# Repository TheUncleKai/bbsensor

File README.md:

# bbsensor
BBQ Sensor

The 8 is a simple temperature monitor intended for BBQ/Smoker. It has 8 inlets that can be used with PTC or Pt100 probes. The BBSensor is run by a ESP8266 Microcontroller (NodeMCU Lua Lolin V3 Modul). The temperature can be delivered either via the display or network.

Front view
![Main View][view1]

Back view
![Back View][view2]

Top view
![Top View][view3]

[view1]: prj/BBSensor_01.png
[view2]: prj/BBSensor_02.png
[view3]: prj/BBSensor_03.png

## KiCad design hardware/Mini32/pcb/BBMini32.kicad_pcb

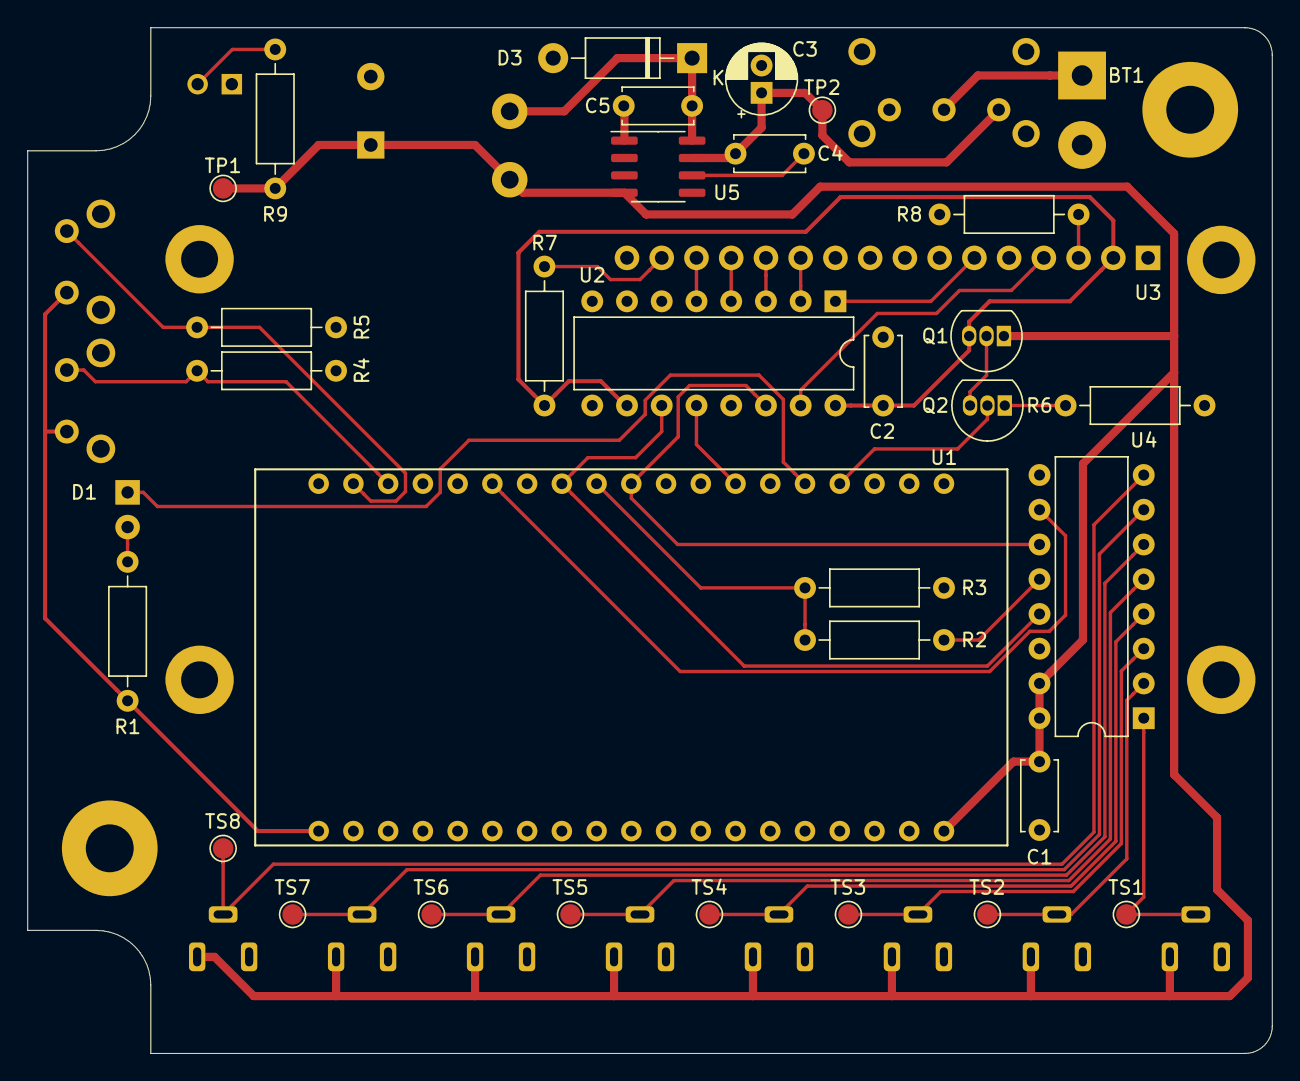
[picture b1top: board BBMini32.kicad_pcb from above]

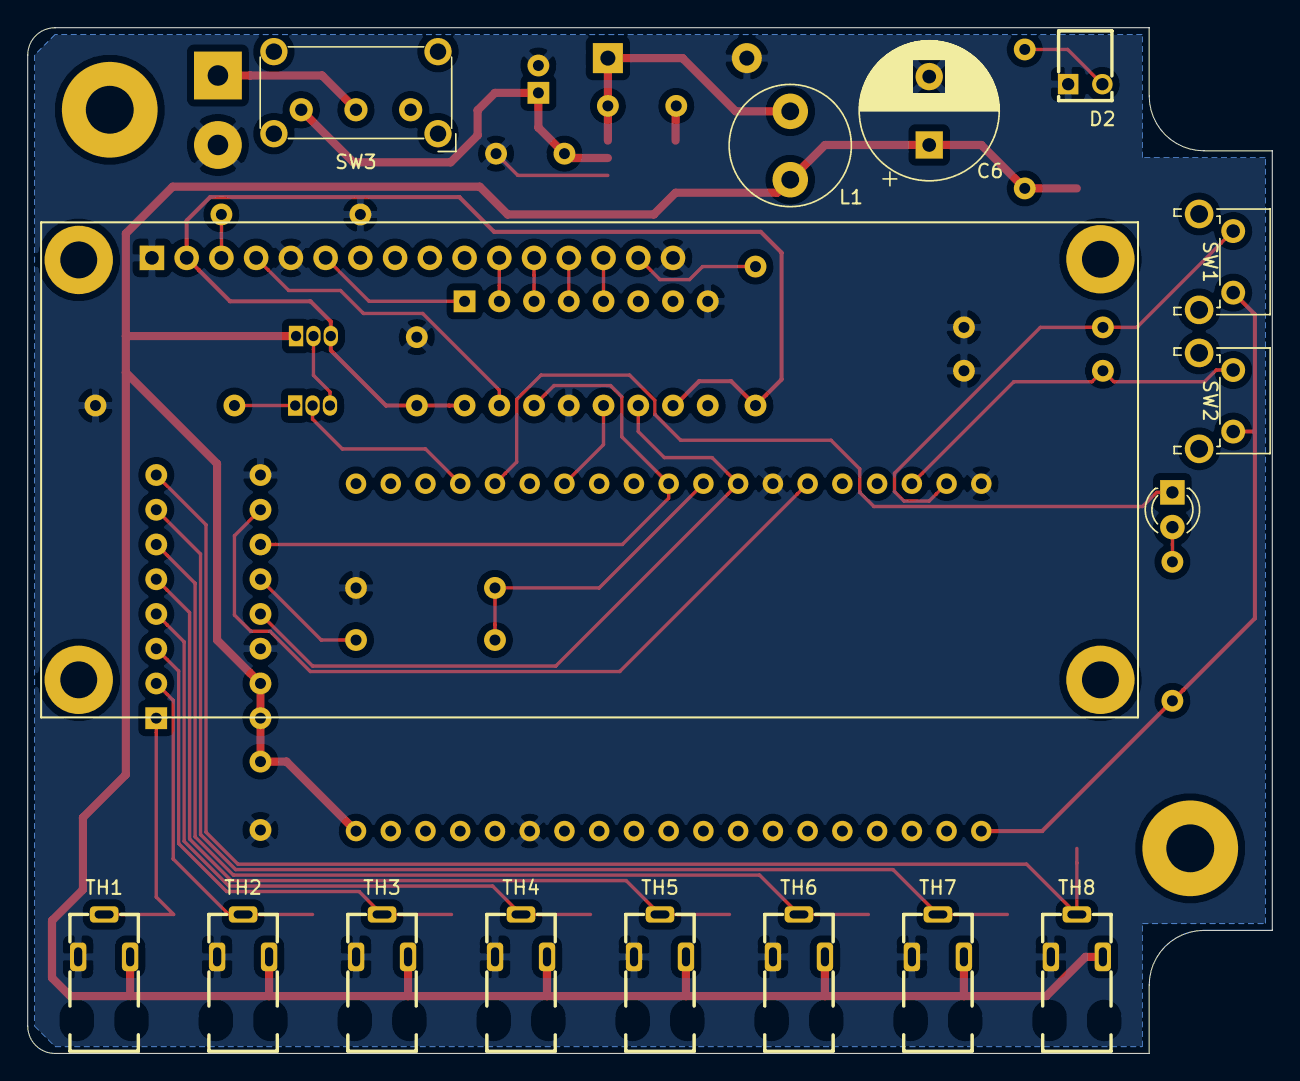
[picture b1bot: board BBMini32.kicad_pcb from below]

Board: 2 copper layers, 91.0 x 75.0 mm, 48 parts (16 on the bottom side), 38 nets.

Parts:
BT1: Battery_Cell; SolderWirePad_1x02_P5.08mm_Drill1.5mm
C1, C2, C4: 100n; C_Disc_D5.0mm_W2.5mm_P5.00mm
C3: 100u; CP_Radial_D5.0mm_P2.00mm
C5: 10n; C_Disc_D5.0mm_W2.5mm_P5.00mm
C6: 68u; CP_Radial_D10.0mm_P5.00mm
D1: GREEN; LED_D3.0mm
D2: POWER; 5600F
D3: 1N5819; D_DO-41_SOD81_P10.16mm_Horizontal
L1: 47u; L_Radial_D8.7mm_P5.00mm_Fastron_07HCP
Q1: S8550; TO-92_Inline
Q2: S8050; TO-92_Inline
R1: 140; R_Axial_DIN0207_L6.3mm_D2.5mm_P10.16mm_Horizontal
R2: 1k; R_Axial_DIN0207_L6.3mm_D2.5mm_P10.16mm_Horizontal
R3, R4, R5: 2k2; R_Axial_DIN0207_L6.3mm_D2.5mm_P10.16mm_Horizontal
R6: 270; R_Axial_DIN0207_L6.3mm_D2.5mm_P10.16mm_Horizontal
R7, R9: 220; R_Axial_DIN0207_L6.3mm_D2.5mm_P10.16mm_Horizontal
R8: 2k; R_Axial_DIN0207_L6.3mm_D2.5mm_P10.16mm_Horizontal
SW1, SW2: SW_Push; SW_Tactile_SPST_Angled_PTS645Vx83-2LFS
SW3: SW_SPDT; SW_E-Switch_EG1224_SPDT_Angled
TH1, TH2, TH3, TH4, TH5, TH6, TH7, TH8: AudioJack3; LUMBERG_1501_05
TP1, TP2: TestPoint; TestPoint_Pad_D1.5mm
TS1, TS2, TS3, TS4, TS5, TS6, TS7, TS8: TestPoint; TestPoint_Pad_D1.5mm
U1: ESP-32_NodeMCU
U2: 74HC595; DIP-16_W7.62mm
U3: HD44780; HD44780_LCD_2x16
U4: MCP3208; DIP-16_W7.62mm
U5: LM2672M-5.0; SOIC-8_3.9x4.9mm_P1.27mm

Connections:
+3V3: R1.1, SW1.2, SW2.2, U1.1
+5V: C1.1, C6.1, L1.2, Q1.1, R9.1, TH1.R, TH2.R, TH3.R, TH4.R, TH5.R, TH6.R, TH7.R, TH8.R, TP1.1, U1.19, U4.15, U4.16, U5.4
/CS1: U1.25, U4.10
/CS2: U1.32, U2.12
/DB4: U2.2, U3.11
/DB5: U2.3, U3.12
/DB6: U2.4, U3.13
/DB7: U2.5, U3.14
/ENABLE: U2.1, U3.6
/MISO: R2.1, U4.12
/MISO_5V: R2.2, R3.1, U1.28
/MOSI: U1.29, U2.14, U4.11
/RS: U2.15, U3.4
/SCLK: U1.27, U2.11, U4.13
/SIGNAL1: TH1.T, TS1.1, U4.1
/SIGNAL2: TH2.T, TS2.1, U4.2
/SIGNAL3: TH3.T, TS3.1, U4.3
/SIGNAL4: TH4.T, TS4.1, U4.4
/SIGNAL5: TH5.T, TS5.1, U4.5
/SIGNAL6: TH6.T, TS6.1, U4.6
/SIGNAL7: TH7.T, TS7.1, U4.7
/SIGNAL8: TH8.T, TS8.1, U4.8
/VDISP: C2.1, Q1.3, R7.1, U2.10, U2.16, U3.2
/VIN: C3.1, C4.1, SW3.3, TP2.1, U5.7
/VPOWER: BT1.1, SW3.2
GND: BT1.2, C1.2, C2.2, C3.2, C4.2, C6.2, D2.1, D3.2, R3.2, R4.2, R5.2, R6.2, R8.2, TH1.S, TH2.S, TH3.S, TH4.S, TH5.S, TH6.S, TH7.S, TH8.S, U1.14, U1.20, U1.26, U2.8, U2.13, U3.1, U3.5, U3.16, U4.9, U4.14, U5.6
unnamed: C5.1, D3.1, L1.1, U5.8
unnamed: C5.2, U5.1
unnamed: D1.1, U1.34
unnamed: D1.2, R1.2
unnamed: D2.2, R9.2
unnamed: Q1.2, Q2.3
unnamed: Q2.1, R6.1
unnamed: Q2.2, U1.35
unnamed: R4.1, SW2.1, U1.22
unnamed: R5.1, SW1.1, U1.21
unnamed: R7.2, U3.15
unnamed: R8.1, U3.3

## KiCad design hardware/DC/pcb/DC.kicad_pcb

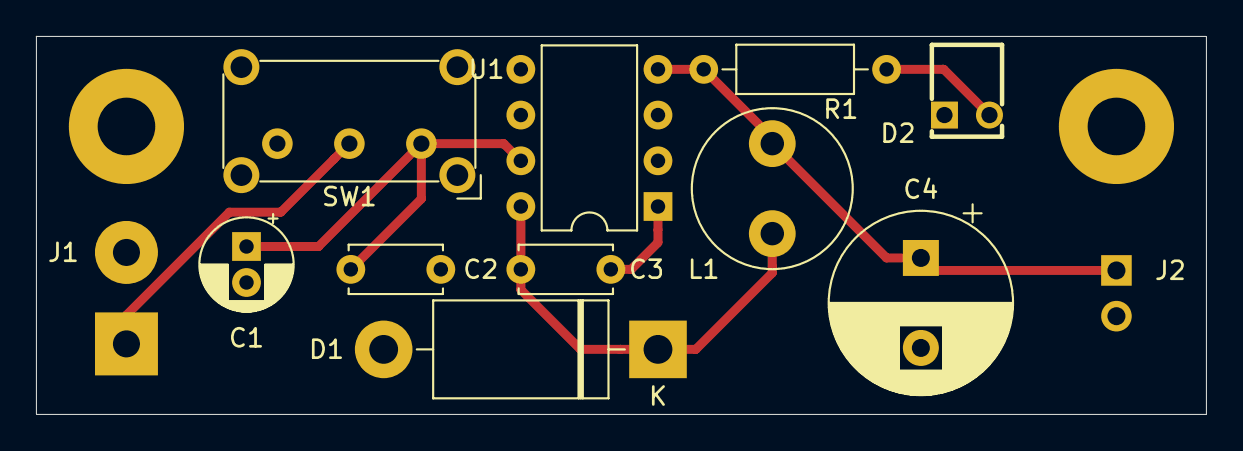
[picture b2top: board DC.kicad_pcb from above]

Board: 2 copper layers, 65.0 x 21.0 mm, 12 parts (1 on the bottom side), 7 nets.

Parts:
C1: 100u; CP_Radial_D5.0mm_P2.00mm
C2: 100n; C_Disc_D5.0mm_W2.5mm_P5.00mm
C3: 10n; C_Disc_D5.0mm_W2.5mm_P5.00mm
C4: 68u; CP_Radial_D10.0mm_P5.00mm
D1: 1N5822; D_DO-201AD_P15.24mm_Horizontal
D2: POWER; 5600F
J1: POWER; SolderWirePad_1x02_P5.08mm_Drill1.5mm
J2: OUTPUT; PinSocket_1x02_P2.54mm_Vertical
L1: 47u; L_Radial_D8.7mm_P5.00mm_Fastron_07HCP
R1: 220; R_Axial_DIN0207_L6.3mm_D2.5mm_P10.16mm_Horizontal
SW1: SW_SPDT; SW_E-Switch_EG1224_SPDT_Angled
U1: LM2672M-5.0; DIP-8_W7.62mm

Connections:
+5V: C4.1, J2.1, L1.2, R1.1, U1.4
/VIN: C1.1, C2.1, SW1.1, U1.7
/VPOWER: J1.1, SW1.2
GND: C1.2, C2.2, C4.2, D1.2, D2.1, J1.2, J2.2, U1.6
unnamed: C3.1, D1.1, L1.1, U1.8
unnamed: C3.2, U1.1
unnamed: D2.2, R1.2

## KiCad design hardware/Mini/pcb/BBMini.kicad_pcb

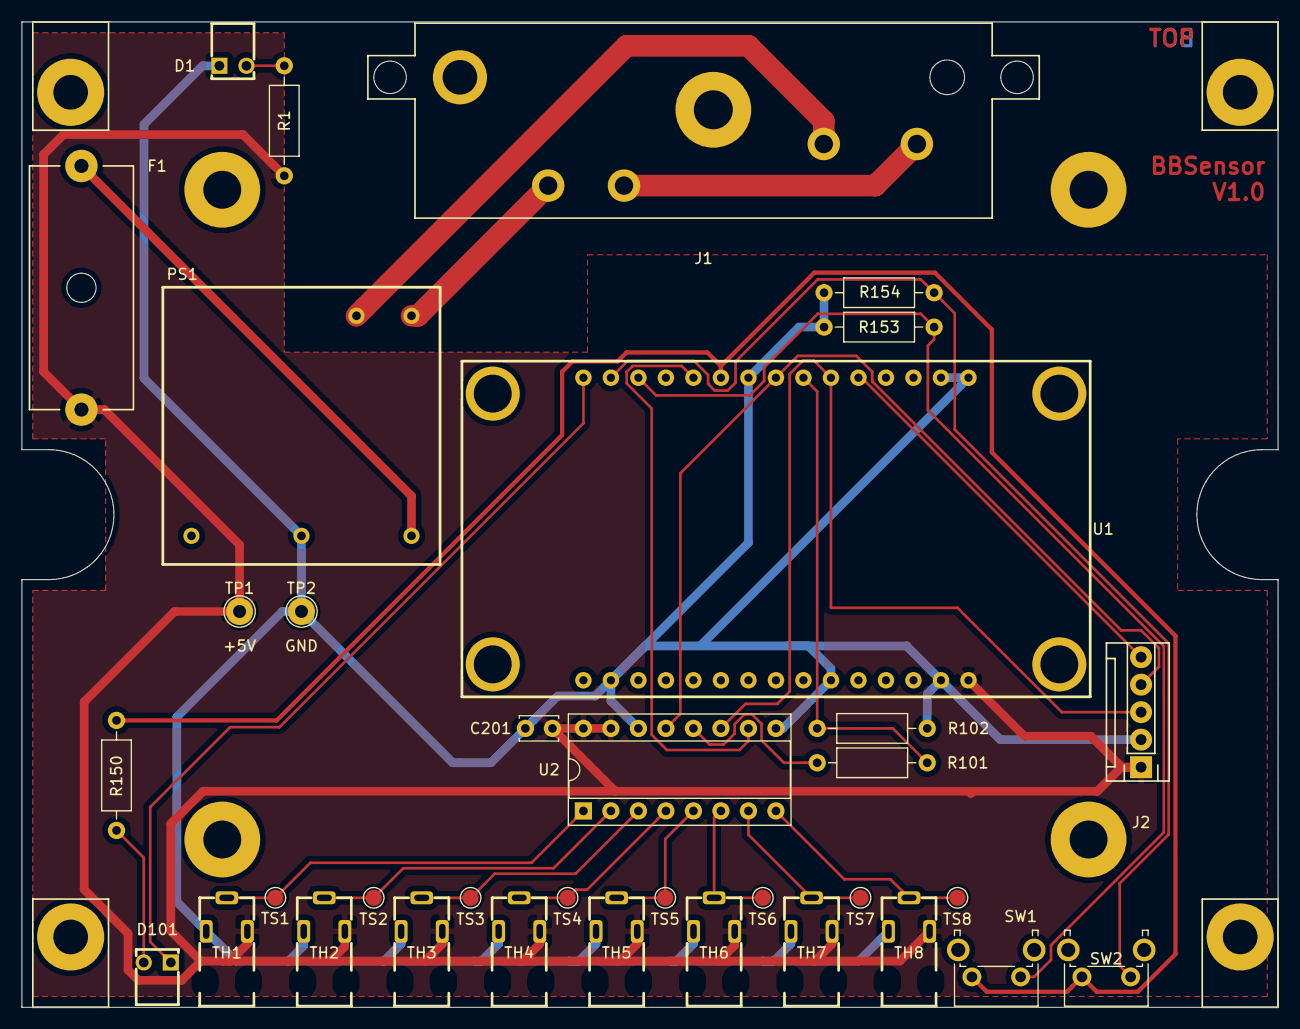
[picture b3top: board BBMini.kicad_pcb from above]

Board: 2 copper layers, 116.0 x 91.0 mm, 35 parts (0 on the bottom side), 26 nets.

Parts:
C201: 100n; C_Disc_D3.4mm_W2.1mm_P2.50mm
D1: POWER; 5600F
D101: GREEN; 5600F
F1: Fuse; Fuse_holder_20x5_22.5
J1: Schurter_CMF1; CMF1_Offset
J2: Display; Molex_KK256_Pin_Header_Straight_1x05
PS1: TMPS_05; Traco_TMPS_05
R1: 220; R_Axial_DIN0207_L6.3mm_D2.5mm_P10.16mm_Horizontal
R101: 1k; R_Axial_DIN0207_L6.3mm_D2.5mm_P10.16mm_Horizontal
R102, R153, R154: 2k2; R_Axial_DIN0207_L6.3mm_D2.5mm_P10.16mm_Horizontal
R150: 140; R_Axial_DIN0207_L6.3mm_D2.5mm_P10.16mm_Horizontal
SW1, SW2: SW_Push; SW_Tactile_SPST_Angled_PTS645Vx83-2LFS
TH1, TH2, TH3, TH4, TH5, TH6, TH7, TH8: AudioJack3; LUMBERG_1501_05
TP1, TP2: TestPoint; TestPoint_THTPad_D2.5mm_Drill1.2mm
TS1, TS2, TS3, TS4, TS5, TS6, TS7, TS8: TestPoint; TestPoint_Pad_D1.5mm
U1: ESP8266-12E_NodeMCU_Lolin
U2: MCP3208; DIP-16_W7.62mm_Socket

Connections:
+3V3: R150.1, SW1.2, SW2.2, U1.21
+5V: C201.1, F1.1, J2.1, R1.2, TH1.R, TH2.R, TH3.R, TH4.R, TH5.R, TH6.R, TH7.R, TH8.R, TP1.1, U1.15, U2.15, U2.16
/Analog/Digital/SIGNAL1: TH1.T, TS1.1, U2.1
/Analog/Digital/SIGNAL2: TH2.T, TS2.1, U2.2
/Analog/Digital/SIGNAL3: TH3.T, TS3.1, U2.3
/Analog/Digital/SIGNAL4: TH4.T, TS4.1, U2.4
/Analog/Digital/SIGNAL5: TH5.T, TS5.1, U2.5
/Analog/Digital/SIGNAL6: TH6.T, TS6.1, U2.6
/Analog/Digital/SIGNAL7: TH7.T, TS7.1, U2.7
/Analog/Digital/SIGNAL8: TH8.T, TS8.1, U2.8
/Analog/Digital/SPI1: J2.3, U1.25, U2.11
/Analog/Digital/SPI2: R101.1, U2.12
/Analog/Digital/SPI3: J2.4, U1.23, U2.13
/Analog/Digital/SPI4: U1.20, U2.10
/Display/SPI5: J2.5, U1.26
/ESP8266/BUTTON1: R153.1, SW1.1, U1.18
/ESP8266/BUTTON2: R154.1, SW2.1, U1.17
/ESP8266/LED: D101.1, U1.16
/ESP8266/MISO: R101.2, R102.1, U1.24
GND: C201.2, D1.1, J2.2, PS1.4, R102.2, R153.2, R154.2, TH1.S, TH2.S, TH3.S, TH4.S, TH5.S, TH6.S, TH7.S, TH8.S, TP2.1, U1.2, U1.10, U1.14, U1.22, U1.29, U1.30, U2.9, U2.14
unnamed: D1.2, R1.1
unnamed: D101.2, R150.2
unnamed: F1.2, PS1.5
unnamed: J1.1, PS1.2
unnamed: J1.2, J1.4
unnamed: J1.3, PS1.1

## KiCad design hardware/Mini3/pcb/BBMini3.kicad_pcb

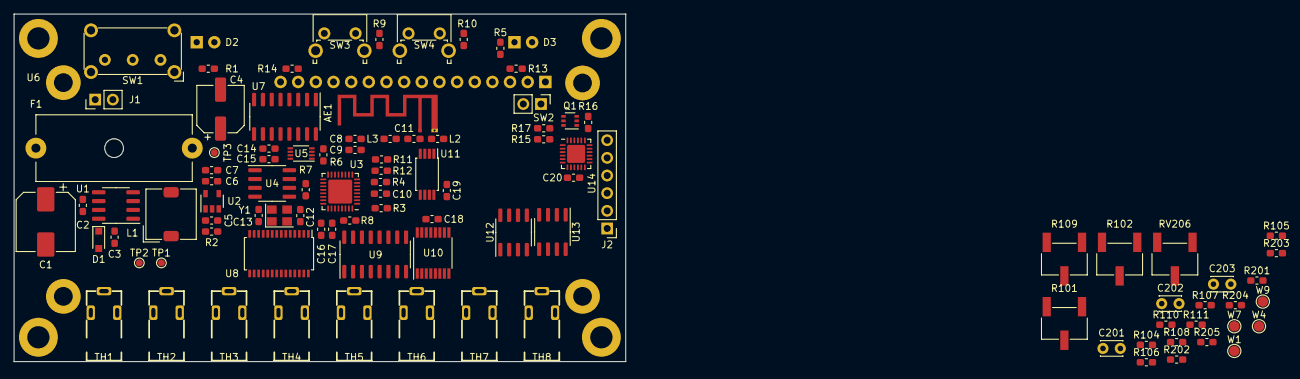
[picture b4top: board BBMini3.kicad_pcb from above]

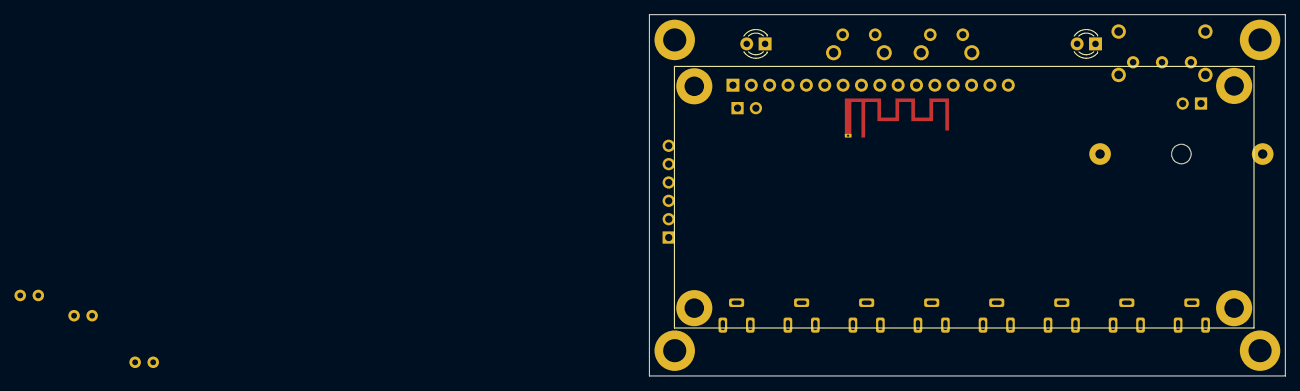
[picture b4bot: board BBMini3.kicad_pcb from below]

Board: 4 copper layers, 88.0 x 50.0 mm, 101 parts (3 on the bottom side), 94 nets, no tracks yet.

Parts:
AE1: Antenna_Shield; Texas_SWRA117D_2.4GHz_Left
C1: 100u; CP_Elec_8x10
C2, C8, C9, C10, C14, C15, C16, C17, C18, C19, C20: 100n; C_0603_1608Metric_Pad1.05x0.95mm_HandSolder
C3: 10n; C_0603_1608Metric_Pad1.05x0.95mm_HandSolder
C4: 68u; CP_Elec_6.3x5.9
C5, C6: 10u; C_0603_1608Metric_Pad1.05x0.95mm_HandSolder
C7: 1u; C_0603_1608Metric_Pad1.05x0.95mm_HandSolder
C11: 5p6; C_0603_1608Metric_Pad1.05x0.95mm_HandSolder
C12, C13: 10p; C_0603_1608Metric_Pad1.05x0.95mm_HandSolder
C201, C202, C203: 100n; C_Disc_D3.0mm_W2.0mm_P2.50mm
D1: 1N5822; D_SOD-323_HandSoldering
D2: POWER; LED_D3.0mm
D3: LED; LED_D3.0mm
F1: Fuse; Fuse_holder_20x5_22.5
J1: Conn_01x02; PinHeader_1x02_P2.54mm_Vertical
J2: USB_B_Mini; PinHeader_1x06_P2.54mm_Vertical
L1: 47u; L_TDK_SLF7032
L2, L3: L; L_0603_1608Metric_Pad1.05x0.95mm_HandSolder
Q1: MBT2222ADW1T1; SOT-363_SC-70-6
R1, R14: 220; R_0603_1608Metric_Pad1.05x0.95mm_HandSolder
R2, R3, R4, R6, R15, R16, R17, R105, R106, R201, R202, R203, R205: 10k; R_0603_1608Metric_Pad1.05x0.95mm_HandSolder
R5: 140; R_0603_1608Metric_Pad1.05x0.95mm_HandSolder
R7, R108, R110: 200; R_0603_1608Metric_Pad1.05x0.95mm_HandSolder
R8: 12k; R_0603_1608Metric_Pad1.05x0.95mm_HandSolder
R9, R10, R12, R104: 2k2; R_0603_1608Metric_Pad1.05x0.95mm_HandSolder
R11: 1k; R_0603_1608Metric_Pad1.05x0.95mm_HandSolder
R13, R111: 2k; R_0603_1608Metric_Pad1.05x0.95mm_HandSolder
R101: 405; Potentiometer_Bourns_3269W_Vertical
R102: 300; Potentiometer_Bourns_3269W_Vertical
R107: 4k7; R_0603_1608Metric_Pad1.05x0.95mm_HandSolder
R109: 470; Potentiometer_Bourns_3269W_Vertical
R204: 100k; R_0603_1608Metric_Pad1.05x0.95mm_HandSolder
RV206: 10k; Potentiometer_Bourns_3269W_Vertical
SW1: SW_SPDT; SW_E-Switch_EG1224_SPDT_Angled
SW2: SW_Push; PinHeader_1x02_P2.54mm_Vertical
SW3, SW4: SW_Push; SW_Tactile_SPST_Angled_PTS645Vx83-2LFS
TH1, TH2, TH3, TH4, TH5, TH6, TH7, TH8: AudioJack3; LUMBERG_1501_05
TP1, TP2, TP3: TestPoint; TestPoint_Pad_D1.0mm
U1: LM2672M-5.0; SOIC-8_3.9x4.9mm_P1.27mm
U2: AP2112K-3.3; SOT-23-5
U3: ESP8266EX; QFN-32-1EP_5x5mm_P0.5mm_EP3.45x3.45mm
U4: AT25SF081-SSHF-X; SOIC-8_3.9x4.9mm_P1.27mm
U5: SN74LVC1G139; VSSOP-8_2.3x2mm_P0.5mm
U6: HD44780; HD44780_LCD_2x16
U7, U9: 74HC595; SOIC-16_3.9x9.9mm_P1.27mm
U8: ADG707; TSSOP-28_4.4x9.7mm_P0.65mm
U10: ADG709; TSSOP-16_4.4x5mm_P0.65mm
U11: MCP3202; TSSOP-8_4.4x3mm_P0.65mm
U12, U13: OPA2340; SOIC-8_3.9x4.9mm_P1.27mm
U14: CP2104; QFN-24-1EP_4x4mm_P0.5mm_EP2.6x2.6mm
W1, W4, W7, W9: TestPoint_Pad_D1.5mm
Y1: ABM8-26.000MHZ-10-1-U-T; Crystal_SMD_Abracon_ABM8G-4Pin_3.2x2.5mm

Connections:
+3V3: C6.2, C7.2, C8.1, C9.2, C10.2, C15.2, C20.1, R3.2, R4.2, R5.2, R6.2, SW3.1, SW4.1, TP3.1, U2.5, U3.1, U3.3, U3.4, U3.11, U3.17, U3.29, U3.30, U4.8, U5.8, U14.5, U14.6, U14.7
+5V: C4.1, C5.2, C14.1, C16.1, C17.1, C18.2, C19.2, L1.2, R1.2, R2.2, R14.1, R102.2, R102.3, R105.1, TH1.S, TH2.S, TH3.S, TH4.S, TH5.S, TH6.S, TH7.S, TH8.S, TP2.1, U1.4, U2.1, U6.2, U7.10, U7.16, U8.1, U9.10, U9.16, U10.14, U11.8, U12.8, U13.8
/ESP8266EX/CS1: U5.6, U11.1
/ESP8266EX/CS2: U5.5, U9.12
/ESP8266EX/DB4: U6.11, U7.2
/ESP8266EX/DB5: U6.12, U7.3
/ESP8266EX/DB6: U6.13, U7.4
/ESP8266EX/DB7: U6.14, U7.5
/ESP8266EX/EN: R4.1, U3.7
/ESP8266EX/ENABLE: U6.6, U7.1
/ESP8266EX/GPIO0: Q1.6, U3.15
/ESP8266EX/GPIO1_TXD: U3.25, U14.20
/ESP8266EX/GPIO2: R6.1, U3.14, U5.1
/ESP8266EX/GPIO3_RXD: R15.2, U3.26
/ESP8266EX/GPIO4: R9.1, SW3.2, U3.16
/ESP8266EX/GPIO5: R10.1, SW4.2, U3.24
/ESP8266EX/GPIO12: R11.2, U3.10
/ESP8266EX/GPIO15: U3.13, U5.2
/ESP8266EX/GPIO16: D3.2, U3.8
/ESP8266EX/LNA: C11.2, L3.1, U3.2
/ESP8266EX/MISO: R11.1, R12.2, U11.6
/ESP8266EX/MOSI: U3.12, U7.14, U9.14, U11.5
/ESP8266EX/RS: U6.4, U7.15
/ESP8266EX/SCLK: U3.9, U7.11, U9.11, U11.7
/ESP8266EX/SDIO_CLK: R7.2, U3.21
/ESP8266EX/SDIO_CMD: U3.20, U4.1
/ESP8266EX/SDIO_DATA_0: U3.22, U4.2
/ESP8266EX/SDIO_DATA_1: U3.23, U4.5
/ESP8266EX/SDIO_DATA_2: U3.18, U4.7
/ESP8266EX/SDIO_DATA_3: U3.19, U4.3
/ESP8266EX/XTAL_IN: C13.2, U3.28, Y1.1
/ESP8266EX/XTAL_OUT: C12.2, U3.27, Y1.3
/ESP8266EX/~RST: Q1.4, R3.1, SW2.1, U3.32
/Processing/PTC1: R201.1, R202.1, U10.5
/Processing/PTC2: R203.1, R204.1, U10.6
/Processing/PTC3: R205.1, RV206.1, RV206.2, U10.7
/Processing/RTD1: R104.2, U10.4, U12.2, U13.3, W4.1
/Processing/RTD2: U10.10, U12.1, U12.5
/Processing/SIGNAL: C201.1, C202.1, C203.1, R101.2, R101.3, R201.2, R203.2, R205.2, U11.2, U13.1, W1.1
/Serial/DTR: Q1.1, R17.1, U14.23
/Serial/RTS: Q1.3, R16.1, U14.19
/Serial/USB_RX: R15.1, U14.21
/Temperature/DA: U8.28, U10.8
/Temperature/DB: U8.2, U10.9
/Temperature/S1A: TH1.R, U8.19
/Temperature/S1B: TH1.T, U8.11
/Temperature/S2A: TH2.R, U8.20
/Temperature/S2B: TH2.T, U8.10
/Temperature/S3A: TH3.R, U8.21
/Temperature/S3B: TH3.T, U8.9
/Temperature/S4A: TH4.R, U8.22
/Temperature/S4B: TH4.T, U8.8
/Temperature/S5A: TH5.R, U8.23
/Temperature/S5B: TH5.T, U8.7
/Temperature/S6A: TH6.R, U8.24
/Temperature/S6B: TH6.T, U8.6
/Temperature/S7A: TH7.R, U8.25
/Temperature/S7B: TH7.T, U8.5
/Temperature/S8A: TH8.R, U8.26
/Temperature/S8B: TH8.T, U8.4
CS0: U5.7, U7.12
GND: AE1.2, C1.2, C2.2, C4.2, C5.1, C6.1, C7.1, C8.2, C9.1, C10.1, C12.1, C13.1, C14.2, C15.1, C16.2, C17.2, C18.1, C19.1, C20.2, C201.2, C202.2, C203.2, D1.2, D2.1, J1.2, J2.5, J2.6, L2.2, L3.2, R8.2, R9.2, R10.2, R12.1, R13.2, R106.1, R111.2, R202.2, R204.2, RV206.3, SW2.2, TP1.1, U1.6, U2.2, U3.33, U4.4, U5.4, U6.1, U6.5, U6.16, U7.8, U7.13, U8.12, U8.27, U9.8, U9.13, U10.3, U10.15, U11.4, U12.4, U13.4, U14.2, U14.25, Y1.2, Y1.4
unnamed: AE1.1, C11.1, L2.1
unnamed: C1.1, C2.1, F1.1, U1.7
unnamed: C3.1, D1.1, L1.1, U1.8
unnamed: C3.2, U1.1
unnamed: D2.2, R1.1
unnamed: D3.1, R5.1
unnamed: F1.2, SW1.1
unnamed: J1.1, SW1.2
unnamed: J2.1, U14.8
unnamed: J2.2, U14.4
unnamed: J2.3, U14.3
unnamed: Q1.2, R16.2
unnamed: Q1.5, R17.2
unnamed: R2.1, U2.3
unnamed: R7.1, U4.6
unnamed: R8.1, U3.31
unnamed: R13.1, U6.3
unnamed: R14.2, U6.15
unnamed: R101.1, R107.2
unnamed: R102.1, R104.1
unnamed: R105.2, R106.2, U12.3
unnamed: R107.1, R108.2, U13.2, W7.1
unnamed: R108.1, R110.2, U12.7
unnamed: R109.1, R111.1
unnamed: R109.2, R109.3, R110.1, U12.6, W9.1
unnamed: U8.15, U9.2
unnamed: U8.16, U9.1
unnamed: U8.17, U9.15
unnamed: U8.18, U9.3
unnamed: U9.4, U10.1
unnamed: U9.6, U10.2
unnamed: U9.5, U10.16

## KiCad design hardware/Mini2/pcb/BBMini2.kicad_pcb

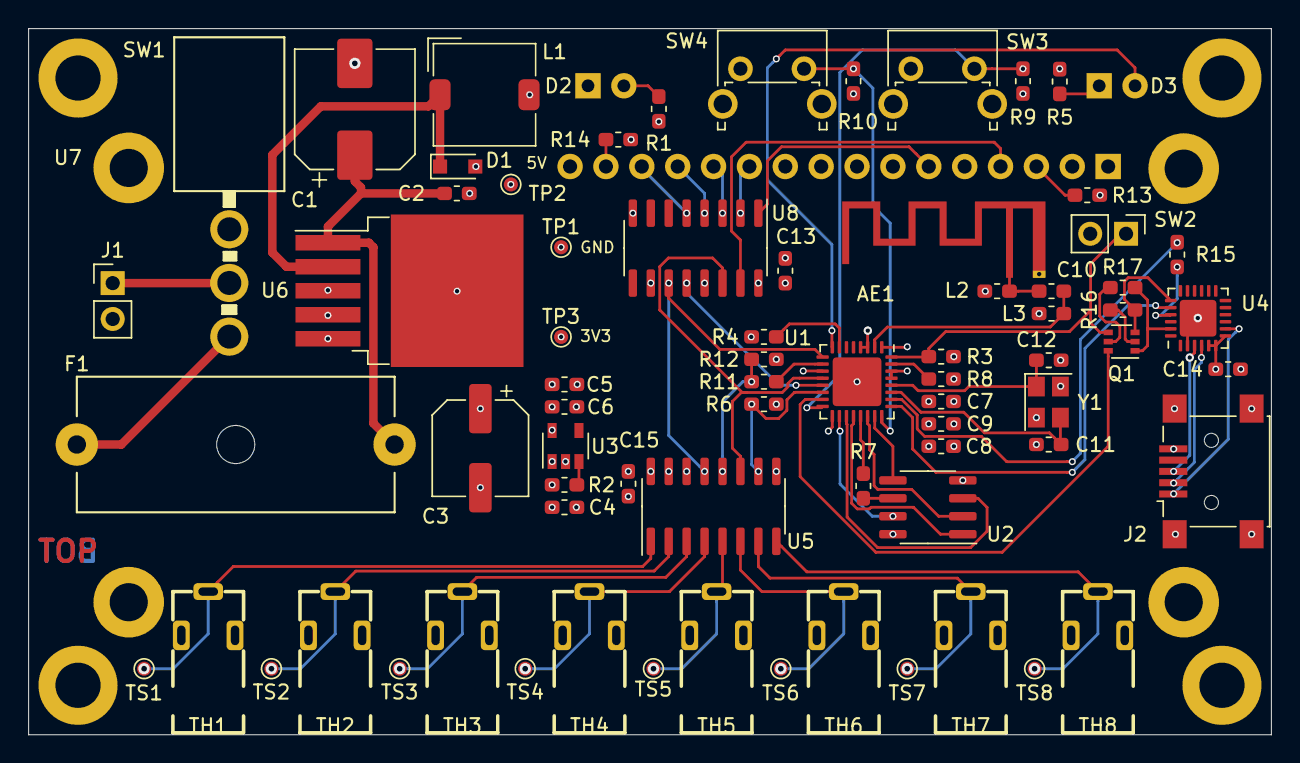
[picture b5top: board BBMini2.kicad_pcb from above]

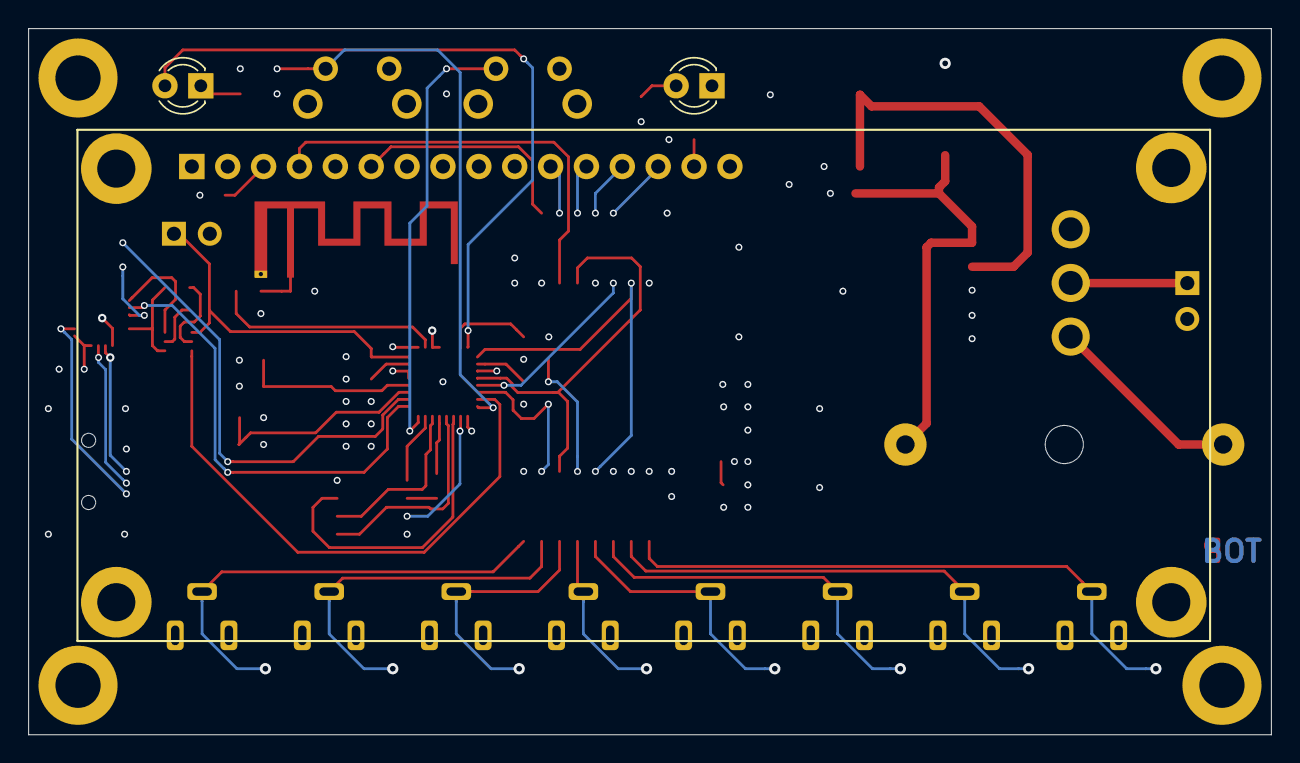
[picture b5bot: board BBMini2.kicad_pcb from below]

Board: 4 copper layers, 88.0 x 50.0 mm, 75 parts (3 on the bottom side), 60 nets.

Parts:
AE1: Antenna_Shield; Texas_SWRA117D_2.4GHz_Left
C1: 100u; CP_Elec_8x10
C2, C7, C8, C9, C13, C14, C15: 100n; C_0603_1608Metric_Pad1.05x0.95mm_HandSolder
C3: 100u; CP_Elec_6.3x5.9
C4, C5: 10u; C_0603_1608Metric_Pad1.05x0.95mm_HandSolder
C6: 1u; C_0603_1608Metric_Pad1.05x0.95mm_HandSolder
C10: 5p6; C_0603_1608Metric_Pad1.05x0.95mm_HandSolder
C11, C12: 10p; C_0603_1608Metric_Pad1.05x0.95mm_HandSolder
D1: 1N5822; D_SOD-323_HandSoldering
D2: POWER; LED_D3.0mm
D3: LED; LED_D3.0mm
F1: Fuse; Fuse_holder_20x5_22.5
J1: Conn_01x02; PinHeader_1x02_P2.54mm_Vertical
J2: USB_B_Mini; USB_Mini-B_Lumberg_2486_01_Horizontal
L1: 100u; L_TDK_SLF7032
L2, L3: L; L_0603_1608Metric_Pad1.05x0.95mm_HandSolder
Q1: MBT2222ADW1T1; SOT-363_SC-70-6
R1, R14: 220; R_0603_1608Metric_Pad1.05x0.95mm_HandSolder
R2, R3, R4, R6, R15, R16, R17: 10k; R_0603_1608Metric_Pad1.05x0.95mm_HandSolder
R5: 140; R_0603_1608Metric_Pad1.05x0.95mm_HandSolder
R7: 200; R_0603_1608Metric_Pad1.05x0.95mm_HandSolder
R8: 12k; R_0603_1608Metric_Pad1.05x0.95mm_HandSolder
R9, R10, R12: 2k2; R_0603_1608Metric_Pad1.05x0.95mm_HandSolder
R11: 1k; R_0603_1608Metric_Pad1.05x0.95mm_HandSolder
R13: 2k; R_0603_1608Metric_Pad1.05x0.95mm_HandSolder
SW1: SW_SPDT; MIYAMA_MS-500-B-VT
SW2: SW_Push; PinHeader_1x02_P2.54mm_Vertical
SW3, SW4: SW_Push; SW_Tactile_SPST_Angled_PTS645Vx83-2LFS
TH1, TH2, TH3, TH4, TH5, TH6, TH7, TH8: AudioJack3; LUMBERG_1501_05
TP1, TP2, TP3: TestPoint; TestPoint_Pad_D1.0mm
TS1, TS2, TS3, TS4, TS5, TS6, TS7, TS8: TestPoint; TestPoint_Pad_D1.0mm
U1: ESP8266EX; QFN-32-1EP_5x5mm_P0.5mm_EP3.45x3.45mm
U2: AT25SF081-SSHF-X; SOIC-8_3.9x4.9mm_P1.27mm
U3: AP2112K-3.3; SOT-23-5
U4: CP2104; QFN-24-1EP_4x4mm_P0.5mm_EP2.6x2.6mm
U5: MCP3208; SOIC-16_3.9x9.9mm_P1.27mm
U6: LM2576S-5; TO-263-5_TabPin3
U7: HD44780; HD44780_LCD_2x16
U8: 74HC595; SOIC-16_3.9x9.9mm_P1.27mm
Y1: ABM8-26.000MHZ-10-1-U-T; Crystal_SMD_Abracon_ABM8G-4Pin_3.2x2.5mm

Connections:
+3V3: C5.2, C6.2, C7.1, C8.2, C9.2, C14.1, R3.2, R4.2, R5.2, R6.2, SW3.1, SW4.1, TP3.1, U1.1, U1.3, U1.4, U1.11, U1.17, U1.29, U1.30, U2.8, U3.5, U4.5, U4.6, U4.7
+5V: C3.1, C4.2, C13.1, C15.2, L1.2, R1.2, R2.2, R14.1, TH1.R, TH2.R, TH3.R, TH4.R, TH5.R, TH6.R, TH7.R, TH8.R, TP2.1, U3.1, U5.15, U5.16, U6.4, U7.2, U8.10, U8.16
/ESP8266EX/CS1: R6.1, U1.14, U5.10
/ESP8266EX/DB4: U7.11, U8.2
/ESP8266EX/DB5: U7.12, U8.3
/ESP8266EX/DB6: U7.13, U8.4
/ESP8266EX/DB7: U7.14, U8.5
/ESP8266EX/EN: R4.1, U1.7
/ESP8266EX/ENABLE: U7.6, U8.1
/ESP8266EX/GPIO0: Q1.6, U1.15
/ESP8266EX/GPIO1_TXD: U1.25, U4.20
/ESP8266EX/GPIO3_RXD: R15.2, U1.26
/ESP8266EX/GPIO4: R9.1, SW3.2, U1.16
/ESP8266EX/GPIO5: R10.1, SW4.2, U1.24
/ESP8266EX/GPIO12: R11.2, U1.10
/ESP8266EX/GPIO15: U1.13, U8.12
/ESP8266EX/GPIO16: D3.2, U1.8
/ESP8266EX/LNA: C10.2, L3.1, U1.2
/ESP8266EX/MISO: R11.1, R12.2, U5.12
/ESP8266EX/MOSI: U1.12, U5.11, U8.14
/ESP8266EX/RS: U7.4, U8.15
/ESP8266EX/SCLK: U1.9, U5.13, U8.11
/ESP8266EX/SDIO_CLK: R7.2, U1.21
/ESP8266EX/SDIO_CMD: U1.20, U2.1
/ESP8266EX/SDIO_DATA_0: U1.22, U2.2
/ESP8266EX/SDIO_DATA_1: U1.23, U2.5
/ESP8266EX/SDIO_DATA_2: U1.18, U2.7
/ESP8266EX/SDIO_DATA_3: U1.19, U2.3
/ESP8266EX/XTAL_IN: C12.2, U1.28, Y1.1
/ESP8266EX/XTAL_OUT: C11.2, U1.27, Y1.3
/ESP8266EX/~RST: Q1.4, R3.1, SW2.1, U1.32
/Serial/DTR: Q1.1, R17.1, U4.23
/Serial/RTS: Q1.3, R16.1, U4.19
/Serial/USB_RX: R15.1, U4.21
/Temperature/SIGNAL1: TH1.T, TS1.1, U5.1
/Temperature/SIGNAL2: TH2.T, TS2.1, U5.2
/Temperature/SIGNAL3: TH3.T, TS3.1, U5.3
/Temperature/SIGNAL4: TH4.T, TS4.1, U5.4
/Temperature/SIGNAL5: TH5.T, TS5.1, U5.5
/Temperature/SIGNAL6: TH6.T, TS6.1, U5.6
/Temperature/SIGNAL7: TH7.T, TS7.1, U5.7
/Temperature/SIGNAL8: TH8.T, TS8.1, U5.8
GND: AE1.2, C1.2, C2.2, C3.2, C4.1, C5.1, C6.1, C7.2, C8.1, C9.1, C11.1, C12.1, C13.2, C14.2, C15.1, D1.2, D2.1, J1.2, J2.5, J2.6, L2.2, L3.2, R8.2, R9.2, R10.2, R12.1, R13.2, SW2.2, TH1.S, TH2.S, TH3.S, TH4.S, TH5.S, TH6.S, TH7.S, TH8.S, TP1.1, U1.33, U2.4, U3.2, U4.2, U4.25, U5.9, U5.14, U6.3, U6.5, U7.1, U7.5, U7.16, U8.8, U8.13, Y1.2, Y1.4
unnamed: AE1.1, C10.1, L2.1
unnamed: C1.1, C2.1, F1.1, U6.1
unnamed: D1.1, L1.1, U6.2
unnamed: D2.2, R1.1
unnamed: D3.1, R5.1
unnamed: F1.2, SW1.1
unnamed: J1.1, SW1.2
unnamed: J2.1, U4.8
unnamed: J2.2, U4.4
unnamed: J2.3, U4.3
unnamed: Q1.2, R16.2
unnamed: Q1.5, R17.2
unnamed: R2.1, U3.3
unnamed: R7.1, U2.6
unnamed: R8.1, U1.31
unnamed: R13.1, U7.3
unnamed: R14.2, U7.15

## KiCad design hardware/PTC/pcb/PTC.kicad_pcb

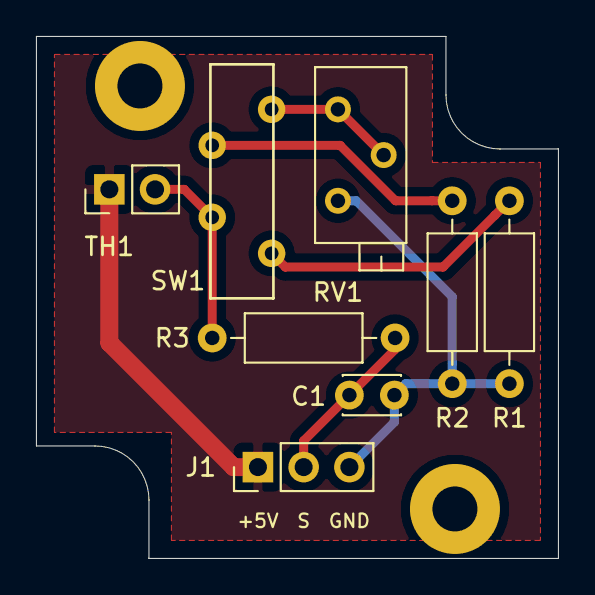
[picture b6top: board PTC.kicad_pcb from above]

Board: 2 copper layers, 29.0 x 29.0 mm, 8 parts (0 on the bottom side), 7 nets.

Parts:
C1: 100; C_Disc_D3.0mm_W2.0mm_P2.50mm
J1: Conn_01x03; PinHeader_1x03_P2.54mm_Vertical
R1, R3: 10k; R_Axial_DIN0207_L6.3mm_D2.5mm_P10.16mm_Horizontal
R2: 100k; R_Axial_DIN0207_L6.3mm_D2.5mm_P10.16mm_Horizontal
RV1: 10k; Potentiometer_Bourns_3296Z_Horizontal
SW1: SW_SP3T; ALPS_SSSS211900
TH1: Thermistor_PTC; PinHeader_1x02_P2.54mm_Vertical

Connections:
+5V: J1.1, TH1.1
/SIGNAL: C1.1, J1.2, R3.2
GND: C1.2, J1.3, R1.2, R2.2, RV1.3
unnamed: R1.1, SW1.4
unnamed: R2.1, SW1.2
unnamed: R3.1, SW1.3, TH1.2
unnamed: RV1.1, RV1.2, SW1.1

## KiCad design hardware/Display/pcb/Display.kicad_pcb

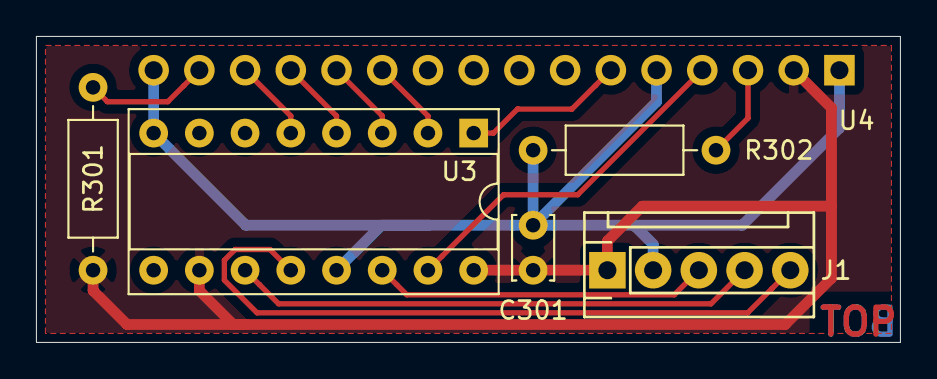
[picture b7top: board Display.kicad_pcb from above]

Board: 2 copper layers, 48.0 x 17.0 mm, 6 parts (1 on the bottom side), 13 nets.

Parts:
C301: 100n; C_Disc_D3.4mm_W2.1mm_P2.50mm
J1: Conn_01x05; Molex_KK256_Pin_Header_Straight_1x05
R301: 220; R_Axial_DIN0207_L6.3mm_D2.5mm_P10.16mm_Horizontal
R302: 2k; R_Axial_DIN0207_L6.3mm_D2.5mm_P10.16mm_Horizontal
U3: 74HC595; DIP-16_W7.62mm_Socket
U4: HD44780; PinSocket_1x16_P2.54mm_Vertical

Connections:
+5V: C301.1, J1.1, R301.1, U3.10, U3.16, U4.2
/CS2: J1.5, U3.12
/DB4: U3.2, U4.11
/DB5: U3.3, U4.12
/DB6: U3.4, U4.13
/DB7: U3.5, U4.14
/ENABLE: U3.1, U4.6
/MOSI: J1.3, U3.14
/RS: U3.15, U4.4
/SCLK: J1.4, U3.11
GND: C301.2, J1.2, R302.2, U3.8, U3.13, U4.1, U4.5, U4.16
unnamed: R301.2, U4.15
unnamed: R302.1, U4.3
